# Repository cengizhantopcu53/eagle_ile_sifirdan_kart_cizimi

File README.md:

# eagle_ile_sifirdan_kart_cizimi
 
https://linktr.ee/cengizhantopcu53

Eagle ile Sıfırdan Kart Çizimi

01 Giriş

02 Eğitim Robotu

03 Çizgi Sensörü

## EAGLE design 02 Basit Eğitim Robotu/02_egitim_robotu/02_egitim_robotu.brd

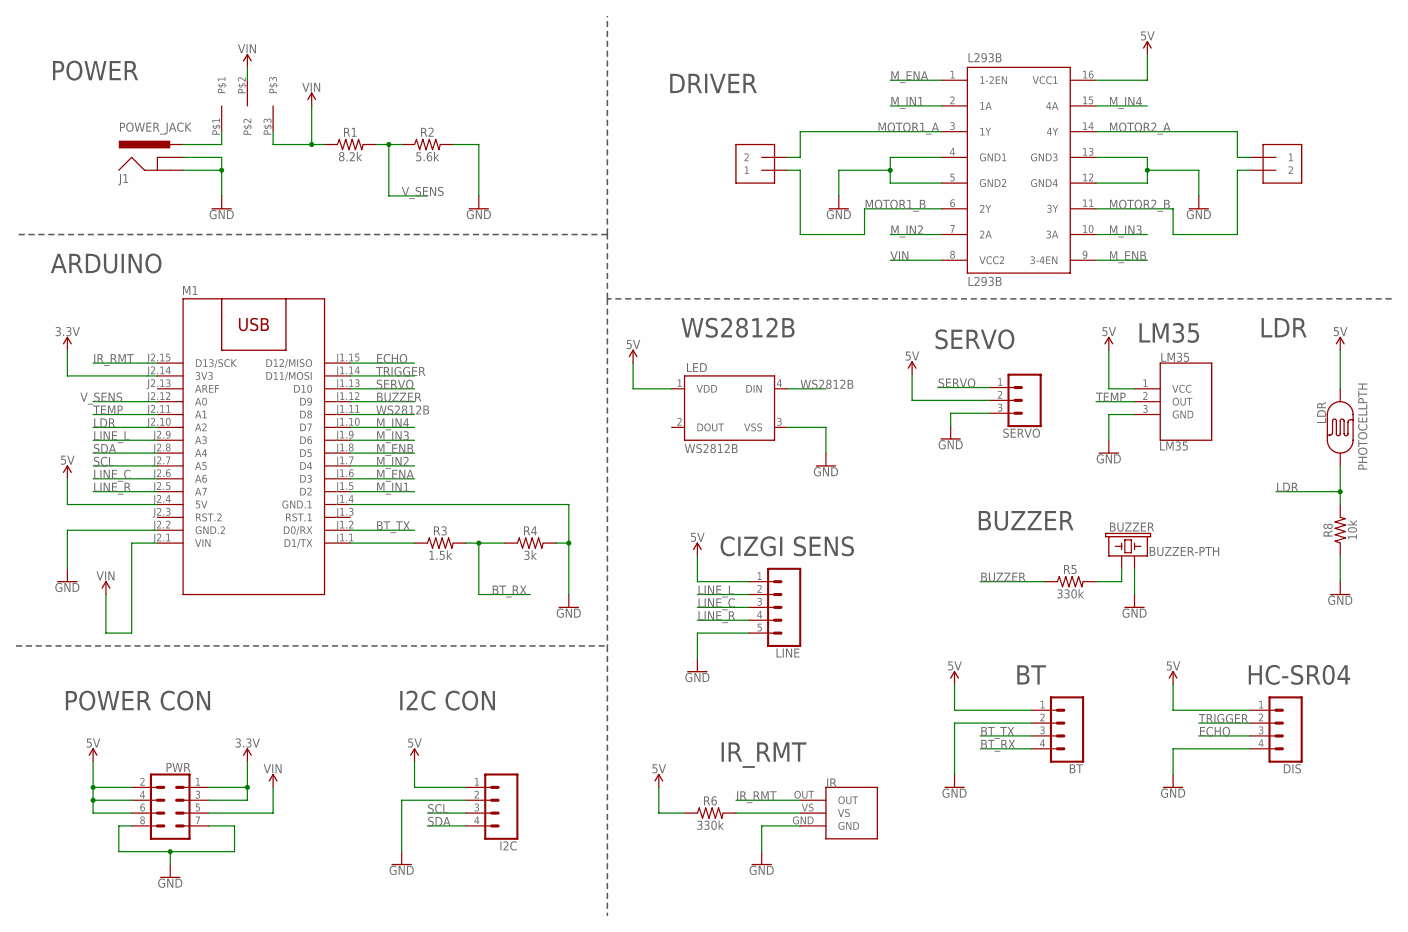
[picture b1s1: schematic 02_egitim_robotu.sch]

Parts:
BT: CONN_04; 1X04
BUZZER: BUZZER-PTH; BUZZER-12MM
DIS: CONN_04; 1X04
I2C: CONN_04; 1X04
IR: TSOP2238THT; TSOP2238
J1: POWER_JACK; POWER_JACK_PTH
L293B: L293B; DIL16
LDR: PHOTOCELLPTH; PHOTOCELL
LED: WS2812B
LINE: CONN_05; 1X05
LM35: LM35; TO-92
M1: ARDUINO-NANO
MPW1, MPW2: 1X2-3.5MM
PWR: CONN_04X2; 2X4
R1: 8.2k; AXIAL-0.3
R2: 5.6k; AXIAL-0.3
R3: 1.5k; AXIAL-0.3
R4: 3k; AXIAL-0.3
R5, R6: 330k; AXIAL-0.3
R8: 10k; AXIAL-0.3
SERVO: CONN_03; 1X03
SW1: SURGULU_SIVIC

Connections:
3.3V: M1.J2.14 (3V3), PWR.1, PWR.3
5V: BT.1, DIS.1, I2C.1, L293B.16 (VCC1), LDR.1, LED.1 (VDD), LINE.1, LM35.1 (VCC), M1.J2.4 (5V), PWR.2, PWR.4, PWR.6, R6.P$1 (1), SERVO.2
ARD_TX: M1.J1.1 (D1/TX), R3.P$1 (1)
BT_RX: BT.4, R3.P$2 (2), R4.P$1 (1)
BT_TX: BT.3, M1.J1.2 (D0/RX)
BUZZER: M1.J1.12 (D9), R5.P$1 (1)
ECHO: DIS.3, M1.J1.15 (D12/MISO)
GND: BT.2, BUZZER.- (2), DIS.4, I2C.2, IR.GND, J1.GND, J1.GNDBREAK, L293B.4 (GND1), L293B.5 (GND2), L293B.12 (GND4), L293B.13 (GND3), LED.3 (VSS), LINE.5, LM35.3 (GND), M1.J1.4 (GND.1), M1.J2.2 (GND.2), PWR.7, PWR.8, R2.P$2 (2), R4.P$2 (2), R8.P$1 (1), SERVO.3
IR_RMT: IR.OUT, M1.J2.15 (D13/SCK)
LDR: LDR.2, M1.J2.10 (A2), R8.P$2 (2)
LINE_C: LINE.3, M1.J2.6 (A6)
LINE_L: LINE.2, M1.J2.9 (A3)
LINE_R: LINE.4, M1.J2.5 (A7)
MOTOR1_A: L293B.3 (1Y), MPW1.2
MOTOR1_B: L293B.6 (2Y), MPW1.1
MOTOR2_A: L293B.14 (4Y), MPW2.1
MOTOR2_B: L293B.11 (3Y), MPW2.2
M_ENA: L293B.1 (1-2EN), M1.J1.6 (D3)
M_ENB: L293B.9 (3-4EN), M1.J1.8 (D5)
M_IN1: L293B.2 (1A), M1.J1.5 (D2)
M_IN2: L293B.7 (2A), M1.J1.7 (D4)
M_IN3: L293B.10 (3A), M1.J1.9 (D6)
M_IN4: L293B.15 (4A), M1.J1.10 (D7)
unnamed: BUZZER.+ (1), R5.P$2 (2)
unnamed: IR.VS, R6.P$2 (2)
unnamed: J1.PWR, SW1.P$1
SCL: I2C.3, M1.J2.7 (A5)
SDA: I2C.4, M1.J2.8 (A4)
SERVO: M1.J1.13 (D10), SERVO.1
TEMP: LM35.2 (OUT), M1.J2.11 (A1)
TRIGGER: DIS.2, M1.J1.14 (D11/MOSI)
VIN: L293B.8 (VCC2), M1.J2.1 (VIN), PWR.5, R1.P$1 (1), SW1.P$2, SW1.P$3
V_SENS: M1.J2.12 (A0), R1.P$2 (2), R2.P$1 (1)
WS2812B: LED.4 (DIN), M1.J1.11 (D8)

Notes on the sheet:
ARDUINO
DRIVER
POWER
POWER CON
I2C CON
IR_RMT
LDR
SERVO
BUZZER
LM35
CIZGI SENS
HC-SR04
WS2812B

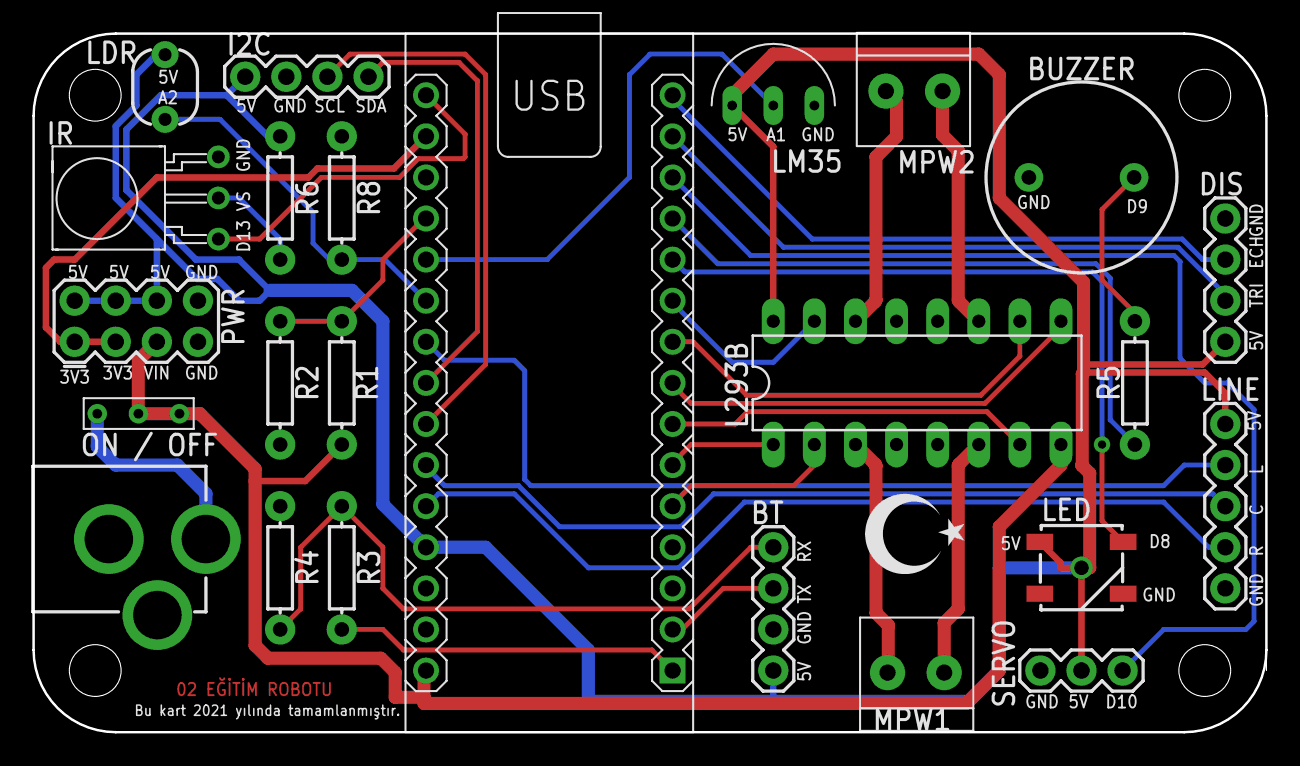
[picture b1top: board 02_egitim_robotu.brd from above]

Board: 2 copper layers, 76.2 x 43.2 mm, 25 parts (0 on the bottom side), 34 nets.

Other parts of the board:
U$9: TR_MINI

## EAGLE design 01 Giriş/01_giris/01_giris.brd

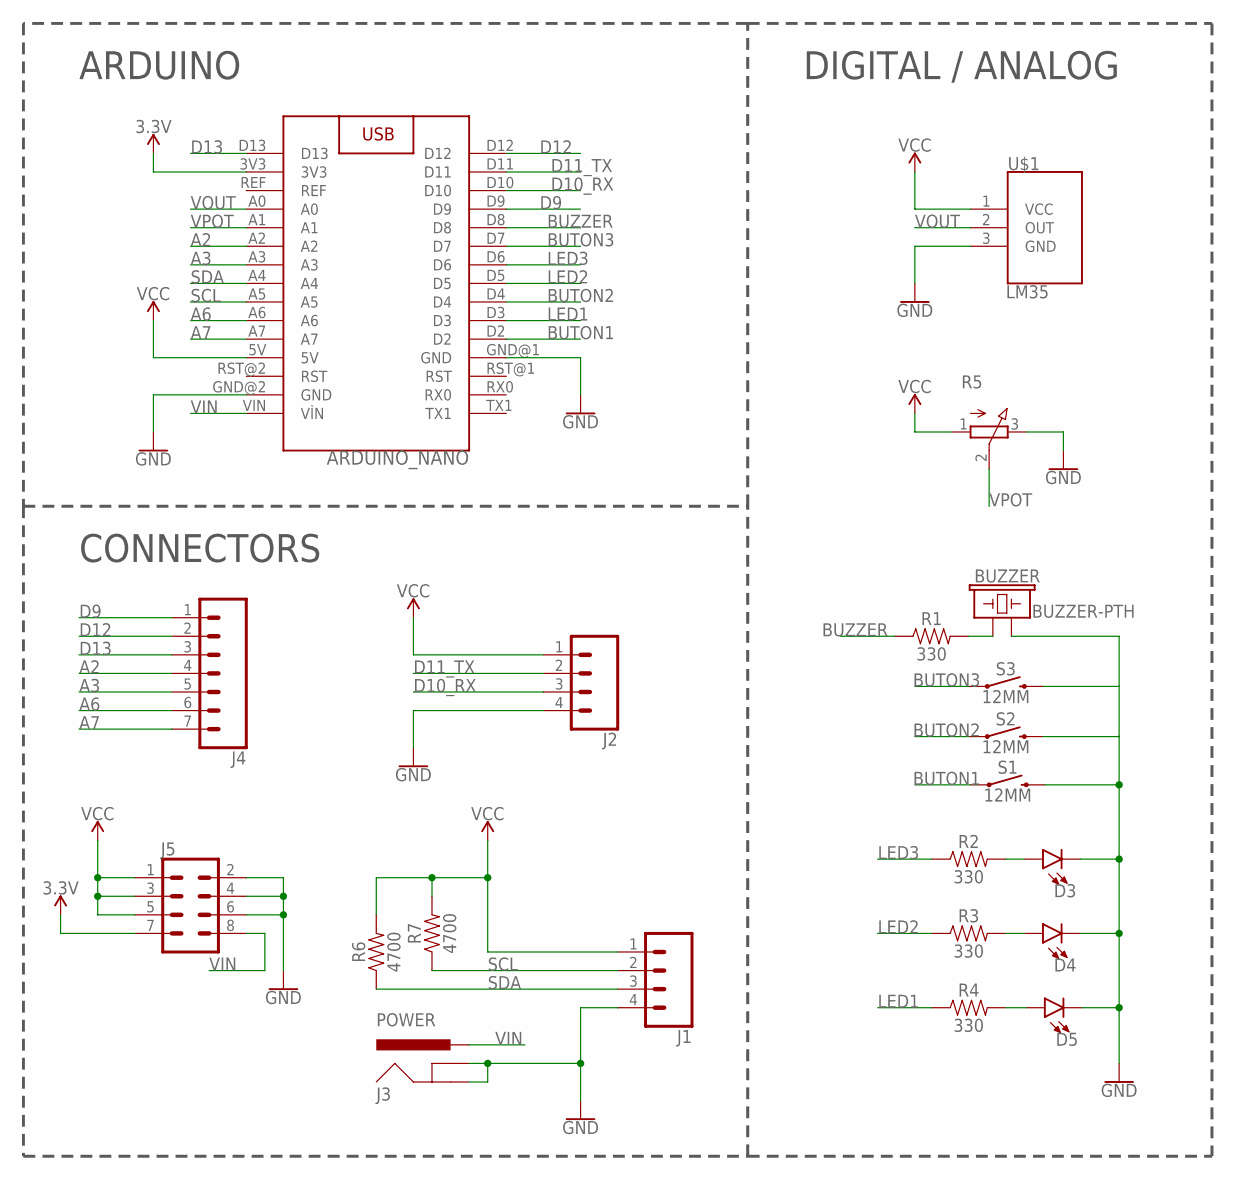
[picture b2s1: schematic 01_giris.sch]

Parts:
ARDUINO_NANO: ARDUINO_NANO
BUZZER: BUZZER-PTH; BUZZER-12MM
D3, D4, D5: LED-3MM-NO_SILK; LED_3MM-NS
J1, J2: CONN_04; 1X04
J3: POWER; POWER_JACK_PTH
J4: CONN_07; 1X07
J5: CONN_04X2; 2X4
R1, R2, R3, R4: 330; AXIAL-0.3
R5: 3RP/1610N
R6, R7: 4700; AXIAL-0.3
S1, S2, S3: 12MM; TACTILE_SWITCH_PTH_12MM
U$1: LM35; TO-92

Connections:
3.3V: ARDUINO_NANO.3V3, J5.7
A2: ARDUINO_NANO.A2, J4.4
A3: ARDUINO_NANO.A3, J4.5
A6: ARDUINO_NANO.A6, J4.6
A7: ARDUINO_NANO.A7, J4.7
BUTON1: ARDUINO_NANO.D2, S1.1
BUTON2: ARDUINO_NANO.D4, S2.1
BUTON3: ARDUINO_NANO.D7, S3.1
BUZZER: ARDUINO_NANO.D8, R1.P$1 (1)
D9: ARDUINO_NANO.D9, J4.1
D10_RX: ARDUINO_NANO.D10, J2.3
D11_TX: ARDUINO_NANO.D11, J2.2
D12: ARDUINO_NANO.D12, J4.2
D13: ARDUINO_NANO.D13, J4.3
GND: ARDUINO_NANO.GND@1 (GND), ARDUINO_NANO.GND@2 (GND), BUZZER.- (2), D3.K (C), D4.K (C), D5.K (C), J1.4, J2.4, J3.GND, J3.GNDBREAK, J5.2, J5.4, J5.6, R5.3 (E), S1.3 (2), S2.3 (2), S3.3 (2), U$1.3 (GND)
LED1: ARDUINO_NANO.D3, R4.P$1 (1)
LED2: ARDUINO_NANO.D5, R3.P$1 (1)
LED3: ARDUINO_NANO.D6, R2.P$1 (1)
unnamed: BUZZER.+ (1), R1.P$2 (2)
unnamed: D3.A, R2.P$2 (2)
unnamed: D4.A, R3.P$2 (2)
unnamed: D5.A, R4.P$2 (2)
SCL: ARDUINO_NANO.A5, J1.2, R7.P$1 (1)
SDA: ARDUINO_NANO.A4, J1.3, R6.P$1 (1)
VCC: ARDUINO_NANO.5V, J1.1, J2.1, J5.1, J5.3, J5.5, R5.1 (A), R6.P$2 (2), R7.P$2 (2), U$1.1 (VCC)
VIN: ARDUINO_NANO.VIN (VİN), J3.PWR, J5.8
VOUT: ARDUINO_NANO.A0, U$1.2 (OUT)
VPOT: ARDUINO_NANO.A1, R5.2 (S)

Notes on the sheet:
ARDUINO
CONNECTORS
DIGITAL / ANALOG

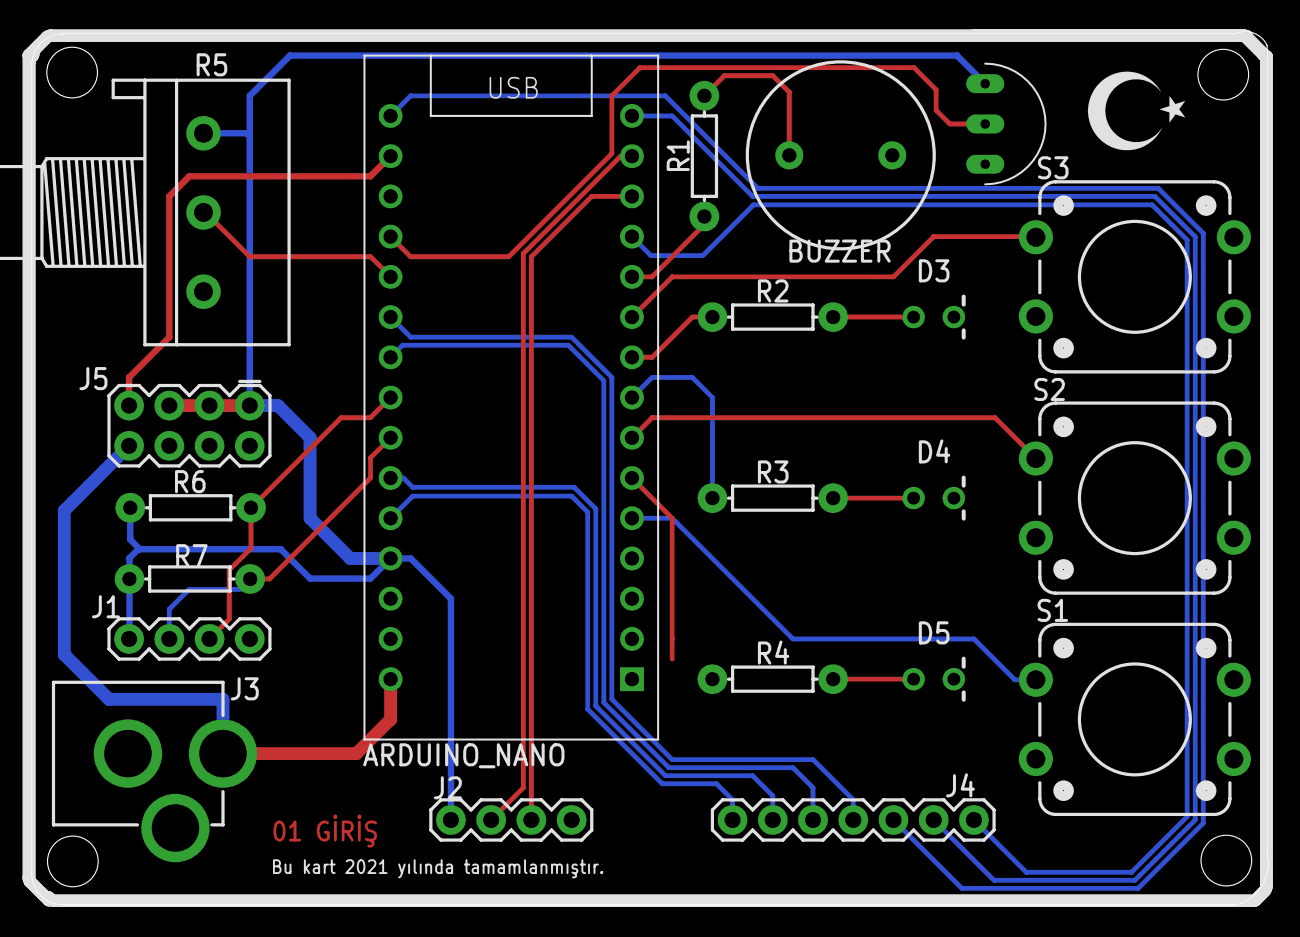
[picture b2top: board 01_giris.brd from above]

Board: 2 copper layers, 78.1 x 55.1 mm, 22 parts (0 on the bottom side), 28 nets.

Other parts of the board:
U$9: TR_MINI

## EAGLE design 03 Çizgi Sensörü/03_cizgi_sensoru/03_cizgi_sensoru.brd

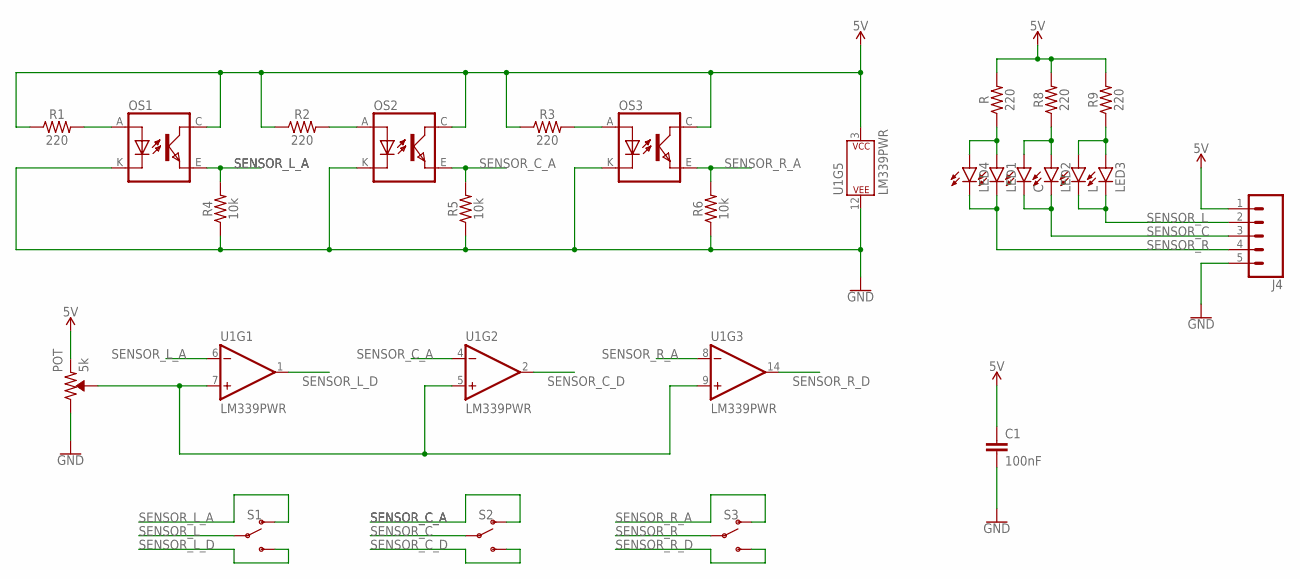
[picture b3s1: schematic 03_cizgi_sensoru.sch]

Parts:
C: LEDSML0805; SML0805
C1: 100nF; 0805
J4: CONN_05; 1X05
L: LEDSML0805; SML0805
LED1, LED2, LED3, LED4: LEDSML0805; SML0805
OS1, OS2, OS3: TCRT5000
POT: 5k; TRIMPOT-SMD-5MM
R, R1, R2, R3, R8, R9: 220; 0805
R4, R5, R6: 10k; 0805
S1, S2, S3: SWITCH-SPDT-SMD-RIGHT-ANGLE; SWITCH_SPST_SMD_A
U1: LM339PWR; TSSOP-14

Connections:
5V: C1.1, J4.1, OS1.C (COLLECTOR), OS2.C (COLLECTOR), OS3.C (COLLECTOR), POT.A (CCW), R.2, R1.1, R2.1, R3.1, R8.2, R9.2, U1.3 (P$V+)
GND: C1.2, J4.5, OS1.K (CATHODE), OS2.K (CATHODE), OS3.K (CATHODE), POT.C (CW), R4.1, R5.1, R6.1, U1.12 (P$V-)
unnamed: OS1.A (ANODE), R1.2
unnamed: OS2.A (ANODE), R2.2
unnamed: OS3.A (ANODE), R3.2
unnamed: POT.B (WIPER), U1.5 (+IN), U1.7 (+IN), U1.9 (+IN)
unnamed: LED1.A, LED4.A, R.1
unnamed: C.A, LED2.A, R8.1
unnamed: L.A, LED3.A, R9.1
SENSOR_C: C.C, J4.3, LED2.C, S2.2
SENSOR_C_A: OS2.E (EMITTER), R5.2, S2.1 (O), U1.4 (-IN)
SENSOR_C_D: S2.3 (S), U1.2 (OUT)
SENSOR_L: J4.2, L.C, LED3.C, S1.2
SENSOR_L_A: OS1.E (EMITTER), R4.2, S1.1 (O), U1.6 (-IN)
SENSOR_L_D: S1.3 (S), U1.1 (OUT)
SENSOR_R: J4.4, LED1.C, LED4.C, S3.2
SENSOR_R_A: OS3.E (EMITTER), R6.2, S3.1 (O), U1.8 (-IN)
SENSOR_R_D: S3.3 (S), U1.14 (OUT)

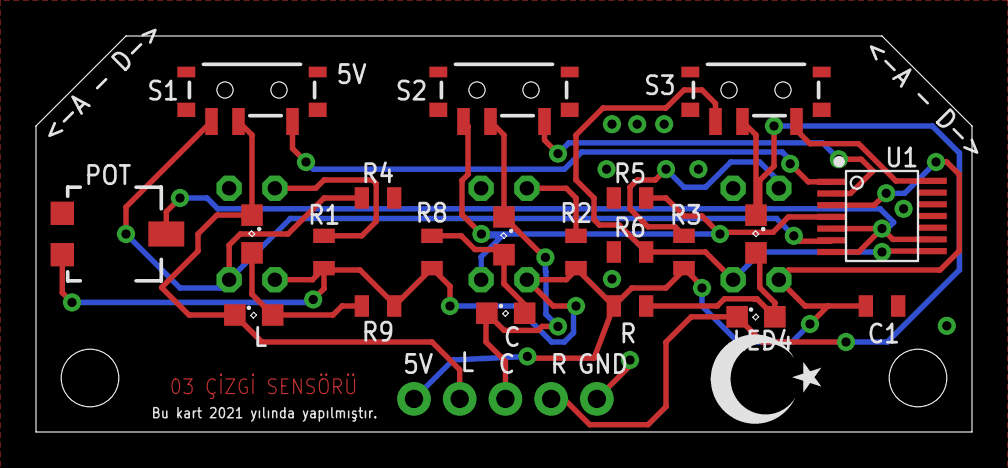
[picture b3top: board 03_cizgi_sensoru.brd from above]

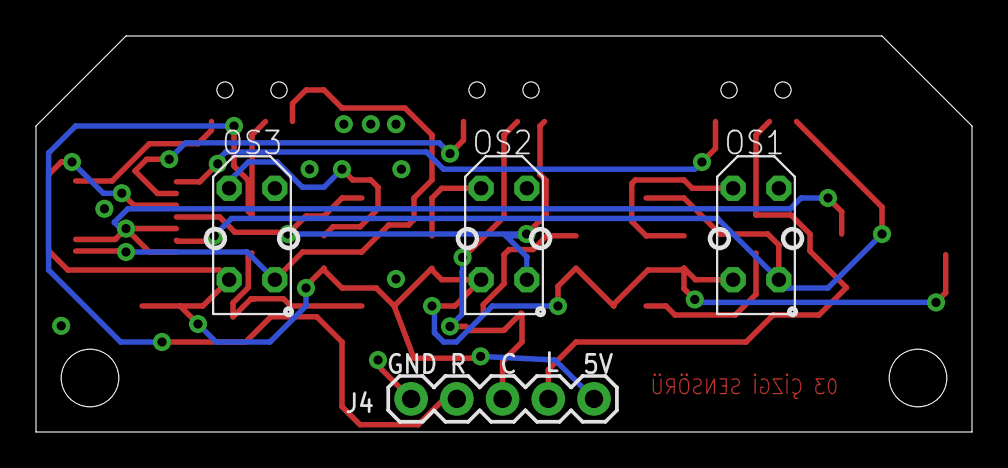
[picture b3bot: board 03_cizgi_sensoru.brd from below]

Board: 2 copper layers, 52.0 x 22.0 mm, 26 parts (4 on the bottom side), 18 nets.

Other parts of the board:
U$5: TR_MINI

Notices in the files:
parts and their libraries:
SparkFun-LED: Licensing: Creative Commons ShareAlike 4.0 International - https://creativecommons.org/licenses/by-sa/4.0
SparkFun-LED: Licensing: CC v3.0 Share-Alike You are welcome to use this library for commercial purposes.
